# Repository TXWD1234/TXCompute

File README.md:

# **TXCompute**
***// Copyright (c) 2026 TXCompute. Licensed under the MIT License.***

TXCompute is a device to perform mathematical calculations. It is targeting to be a more powerful calculator, that don't only rely on buttons, but can handle complicated logic.
*This project is for the hackathon event [Fallout](https://fallout.hackclub.com) hosted by [Hackclub](https://www.hackclub.com).*

# Project Usage

## What it does
TXCompute device has a screen and USB ports that allow user to connect a USB keyboard to it, and input to a terminal-like text editor displayed by the screen. 

The input of user will be processed by a command line parser, which can handle simple commands, as well as TXCSL code.
If user input is TXCSL code, it will be forward to the TXCSL engine, which executes the input code, and outputs the execution result.

## How to use it
**To provide power:**
- Plug in an USB-C cable connecting with power into the USB-C socket

**To connect with keyboard:**
- Plug in an USB-A cable connecting with the keyboard (for wired keyboard) / wireless receiver (for wireless keyboard) into the USB-A socket

**To boot the device:**
- Press the power button on the device until the device is booted.

**To shutdown the device:**
- Enter `exit` or `shutdown` in the terminal
  ```
  exit
  shutdown
  ```
- or Press the power button until the device is shutdowned

**To perform a TXCSL calculation:**
- Enter the expression in the terminal directly
  ```
  1 + 2 * (5 + 2)
  ```
- or With prefix `csl`
  ```
  csl 1 + 2 * (5 + 2)
  ```

## How to build it
### Preparation
#### Hardware Parts
- An ESP32-S3-DevKitC-1 Devboard
- A LCD Screen that is 480x320px sized, and supports Parallel 8080 (i80) and ILI9488
- An USB-C receptacle
- An USB-A receptacle
- A push button
- A MOSFET Transistor
- 4 NPN Transistor
- 2 capacitors: 0.1uf, 10uf
- Several resistors: 10k, 5.1k
- Several wires

*See detailed information in [BOM](https://github.com/TXWD1234/TXCompute/blob/main/BOM.csv)*

#### Hardware Environment
- 3D Printer
  - Several filament
- Soldering Iron
  - Several solder

#### Software Environment
- ESP-IDF
- CMake
- Git
- TXLib
- (Optional) VSCode (With ESP_IDF plugin)
- (Optional) KiCad
- (Optional) Fusion
- (Optional) OrcaSlicer

### Procedure
#### Part 1: Shell
*Working Directory: `/Hardware/CAD`*
1. Use OrcaSlicer to process a component (an individual body) in the `Main.step` file
2. Send the result to your 3D printer
3. Wait for print to finish, and repeat for every component

#### Part 2: Software
*Working Directory: `/Software`*
1. Open the directory with VSCode
2. Connect the ESP32 Devboard to your computer
3. Run command `ESP-IDF: Build, Flash and Start a Monitor on Your Device` in VSCode:
   1. Ctrl+Shift+P open the palette
   2. Enter the command title `ESP-IDF: Build, Flash and Start a Monitor on Your Device`

#### Part 3: PCB
*Working Directory: `/Hardware/PCB`*
1. Contact a manufacturing company to fabricate the PowerButton PCB
   - Use the Gerber files in directory: `PowerButton/Gerbers`
   - Suggestion: Do this part in China

#### Part 4: Assembly
*Working Directory: `/Hardware`*
1. Place the ESP32 Devboard and the PowerButton PCB on their according foundation
   - Use screws to secure the mounting
2. Connect the components except the screen, according to the schematic: `PCB/Fallout.kicad_sch`
   1. Connect each pin of the USB-C receptacle to their respective GPIO pin
   2. Connect each pin of the USB-A receptacle to their respective GPIO pin
   3. Connect each pin of the PowerButton receptacle to their respective GPIO pin
3. Assemble the Hinge  

   1. Slide body Hinge_Left onto body Hinge_Edge_Left, such that the through hole of Hinge_Left is containing the extruding cylinder of Hinge_Edge_Left
   2. Slide body Hinge_Center_Left into the other side of Hinge_Left, such that the through hole of Hinge_Left is also containing the extruding cylinder of Hinge_Center_Left  

   3. Do the same thing with Hinge_Right, Hinge_Edge_Right and Hinge_Center_Right
   4. Slide each of the assembled hinge component onto body Screen/Body. Make sure the sunmao structure on the Hinge_Edge_* fit
   5. Insert the tenon part of the sunmao structure (body group: Hinge_Body_Connection) into the mortise in center created by the 4 overlaping rectangle holes
4. Connect the 2 main bodies
   1. Secure the hinge on the MCU/Body with screws in the indicated screw holes
   2. Run wires from the ESP32 through the hinge to the screen
5. Place the LCD Screen on it's foundation in the Screen/Body
   1. Place the LCD Screen
   2. Place the Cover (Body Cover) on top of the LCD Screen
6. Place the back plate (body MCU/Bottom)
   - Screw in the screws in the indicated location

# Project Story (Why it exists)
> *"Lower, lower, lower..."*

## My Programming Obsession
From the first day I started programming, I found myself constantly pursuing a direction involuntarily.
And that direction is **low level**.
Where I first started was already pretty low: C++ is almost everyone think the lowest.
But I am not satisfied with that.
Exploring more lower level things such as Windows API and OpenGL, while making my own library and creating data structures, considering architecture, building complex systems and engines... I am on the way toward the lowest level.

## Where Did TXCompute Came From
When I first heard about this hardware hackathon: Fallout, and the fact that I need to make a hardware project, the first thing I thought about is **calculator**.
This is the first time I tried hardware development; before I used to think that hardware are all logic gates.
And I thought using logic gates to make something would be really cool, and a really interesting challange.
In this case, a calculator would be a perfect project to do that. Implement the most basic adder, subtractor, and multiplier are exactly the tasks I was imagining.
Therefore I set my goal, and started reseaarching.

## The Design Struggle
After a bit of research, I quickly found out that there are way too many obstacles to achieve my original idea, therefore made it impossible.
The major problem is that logic gates are... kind of way too low, making them very hard to connect with other existing infrastructure.
After that realization, I was stuck in a design idea struggle. A design struggle about what I should make.
Not using logic gates just made everything feels so simple. MCUs can just perform the calculation, the entire project idea of a calculator just suddenly seems to be too easy and not impressive enough.
**I was worried about the project being too simple.**
For almost a week, I did not know what to do.
I was numbing myself by exploring hardware programming environment and new knowledge, but knowledge without usage is useless. And everytime I think about the project the only thing I felt is dilemma...
Until I finally found an solution. I do not need to make exactly the project I was planning to make before.
**If making the basic is too easy, then just expand on the basic.**
> **"Make it advanced, make it better."**

This is my conclusion. If just make a basic calculator is too easy with MCU, then make a better calculator, that has more feature, more capability, and faster.
When I realized that, I immediately had an idea:
Make a computation DSL, and an emulator for it.
Write a compiler and a virtual machine in the tight memory and performance constrained environment of embedded system is definitely hard enough... I thought.
So then, I start working.

## Back to Low Level
After 2 month of hardworking, TXCompute finally came close to the end.
During development, I found out that the project is actually not as simple as I thought.
The memory constraint really made software became a struggle. Architecture and structure design need to have awareness of the memory constraint, therefore much more complicated. I made several new data structure during development, and the entire project software design is also heavily optimized for tight memory.
At the very last, in the process of finishing up the project, I suddenly found out there is a unplanned component in the project: The PowerButton.
Brief explaination about the component: It is a hardware push button controling the power input of the device, but at the same time need to be able to be turned off by the software.
And as I developed deeper into this component, I learned the mechanics of transistors, and built logic gates (the NOT gate specificly) with it. Finally I utilized all these knowledge and created a PCB.
That's when I realized. I am back at what I was imagining at the start of the project: interact and make things with logic gates.
Additionally, even lower! I made the logic gate itself!
And that is exactly the pursuit of this project, as well as my programming career:
> *Lower, lower, and lower....*

# Credit
Auther: [TX_Jerry](https://www.github.com/TXWD1234)  
Assistant: [Justin Li](https://www.github.com/justinnova0915)  
Art Inspiration: The Matrix  
Event: [Fallout](https://fallout.hackclub.com), hosted by [Hackclub](https://www.hackclub.com)  
// Project by TXStudio  

# Project Documentation

This project consist of 4 main parts:
- The Hardware Assembly
- Fireware Infrastructure
- Terminal Engine
- TXCSL Languge Processor

And finally the `MainClass` that combines everything together.

*The purpose of this documentation is to provide an overview of the implementation, and an entry point of understanding the logic.*
*To understand the detailed logic, please read the source code, and take reference to the comments.*

## The Hardware Assembly

The TXCompute device, or the *"TXComputer"* consists of 2 parts:
- The 3D Printed Shell
- Circuit
- Hardware Parts

### Shell
*The 3D shell design took inspiration from my personal laptop: `Legion Y7000 IRX10`.*
The 3D printed shell is the hardware container containing all the wire connection from the circuit, who acts like the interface of the project for users.
The model design is highly focused on mechanical functionalities. Its implementation consists of:
- Hinge
- Circuit Foundation - support the wiring and the PCB to sustain it's position
- Several Connections
  - connect the screen to teh shell
  - connect the screen part to the hinge
  - connect the MCU part to the hinge
  - connect the front and back plate to the MCU part

*Highlight worth mentioning: The usage of sunmao in the connection.*

#### Hinge Design
The hinge is designed such that wires connecting the ESP32 and the screen (the display bus) can run through.
It has 2 hollow cylinders, one containing the other. The smaller one will be containing the wires.
The hinge allow a maximum rotation of 126 degree, and is physically stop by the MCU body when reached the limit. (Have to create a physical stop to prevent the hinge from laying flat because the material of 3D printing filament is neither strong enought nor accurate enough to make an actual self lock hinge.)

### Circuit
There are 2 main parts for the circuit: parts connection and the power button.

#### Parts Connection
Connect the components including:
- LCD Screen
- PowerButton
- USB-A / USB-C receptacle
to the ESP32 devboard.

#### PowerButton
The logic circuit that controls the power and life time of the device.
The circuit allow a push button to turn on and off the device, while when turned on, device can turn itself off as well.

## Firmware
*Also known as TXESP_Infrastructure.*

There are 4 branches in the firmware infrastructure, each serve a usage in the main class:
- TextRenderer
- USBKeyboardInputHandler
- Buffer
- PowerManager

### TextRenderer
TextRenderer is the highest level interface of the rendering pipeline, that is based off of the ILI9488 driver and ESP_LCD.
The dependency tree:
```
TextRenderer
FrameComposer
ILI9488DriverPanel
ESP_LCD
```

#### `ILI9488DriverPanel`
*This Driver is made according to the data sheet: https://www.hpinfotech.ro/ILI9488.pdf*
*It's basically just a wrapper of the io system.*
ILI9488DriverPanel manage the lowest level communication between the higher level firmware and the LCD screen hardware.
It has stores the commands to the hardware, and specificly focuses on these two jobs:
- Initialization of the LCD screen;
- Write data to specific location of the LCD screen's framebuffer.

Call `ILI9488DriverPanel::init()` to initialize; Call `ILI9488DriverPanel::draw()` to write pixels.

#### `FrameComposer`
Manage the bus and io, and also wraps around the `ILI9488DriverPanel`, bringing the render process one level higher.
It takes care of the transformation of the pixel data, manage the lifetime of the bus and io provided by ESP_LCD.
`FrameComposer` is the end of talking to hardware APIs. It fully wraps the configuration and initialization, leaving only an API `draw(Coord topLeft, Coord dimension, u16* data)` for the software to perform the rendering.

#### `TextRenderer`
Manage the pixel data, consists of a simple double buffer design, and the job of unpacking the bit-packed character data.
`TextRenderer` abstract the rendering pipeline one step furthur, now the software don't need to thing about the actual pixel data anymore, instead only the character that is being drawed need to be considered.
*This class is technically a software as it does not use hardware APIs directly, but I still considered it as firmware because it is such a low level component.*

#### Font
Because of the limited storage of ESP32, the font data is stored in bitmap, bit packed as one bit is one pixel.
The font data is in the form of a C array in hex with type `u8`, in a header file, along with a `size_t` constant containing the size of the font data, all in `constexpr const`.
The header file will be included by the user of the font.

The font file used in this project is generated by a 2 stage pipeline:
- convert ttf file into png file via a python script
- read the png image file and pack the color into bits via a C++ program

### USBKeyboardInputHandler
USBKeyboardInputHandler is the highest level interface of the keyboard input pipeline. It is based on HID and ESP's USB framework.
The dependency tree:
```
USBKeyboardInputHandler
USBFramework
ESP_USB; ESP_HID
```

#### `USBFramework`
Simplifies the pipeline of USB Host.
`USBFramework` provide a set of simplified init / uninit APIs to manage the driver and interface APIs.
It is simply just a wrapper around ESP_USB's API.

#### `USBKeyboardInputHandler`
*This class is made according to the data sheet: https://usb.org/sites/default/files/hut1_5.pdf*
*USBFramework is a generalized USB framework that work for any type of usb connection, while `USBKeyboardInputHandler` is made specificly for HID keyboard input.*
`USBKeyboardInputHandler` provide the interface and driver callback to the `USBFramework` to receive keyboard input.
After received the raw keyboard input report, `USBKeyboardInputHandler` also map the raw data into a custom key code set.
It also manages the pressing state of each key, tracking the state of each key pressed.
At the end, every time an report is updated, an user callback provided by the user of this class will be called with the parameter of the information of this key press event.
The overall design took inspiration and reference from GLFW 3. *Credit: `https://www.glfw.org`.*
`USBKeyboardInputHandler` is also a global state machine, adopted the design of *"pure static class"* from `USBFramework`.

#### Driver
Contains the implementation of `driverCallback_impl` and `interfaceCallback_impl`, as the lifetime manager of the process.
Also contain the essential enum types such as `Key`, `Action` and `Mod`, as well as `keyCodeTable`, which is the lookup table describing the translation between HID code and a uniformed code set that's corresponding to ASCII.

#### Logic
Handles:
- The decode process of the Modifiers
- The Action state
  - Release
  - Repeat
  - Press
- Current pressing key
  - Key cache
The core entry function is `handleReport_impl()`, which is being called by the `interfaceCallback` when an keyboard input event happens.

#### Interface
The user is only exposed to 3 functions:
- `init()`
	Initialize the entire system, including the `USBFramework`. *(it's actually just initing `USBFramework` but.. it's just for encapsulation)*
- `uninit()`
	Uninitialize the entire system, including the `USBFramework`.
- `setCallback(InputCallbackFunc_t func)`
	Set the event callback when a keyboard input event happens.

**`InputCallbackFunc_t`**:
```cpp
using USBKeyboardInputHandler::InputCallbackFunc_t = void (*)(
	USBKeyboardInputHandler::Key,
	USBKeyboardInputHandler::Action,
	USBKeyboardInputHandler::Mod); // key, action, mod
```

### Buffer
`buffer.hpp` is an wrapper around ESP_HEAP_CAPS, that provide a generalized API `allocate` and `free` with template to manage memory.
It also provide the memory managing wrapper for a few data structure from TXLib that are used in the project, including:
- `Buffer_GrowArray`
- `Buffer_CircularQueue`
- `Buffer_RingBuffer`

And a plain memory container `Buffer`.

### PowerManager
`PowerManager` is a small class that wraps the ESP_GPIO APIs, especially the intiialization setup, and gave the user a fast way to operate an pin's charge (voltage).
It is designed targeting to serve the power button functionality of the project.

## Terminal Engine

The Terminal Engine is a text render and input processor, that performs resemble a terminal.
It is designed targeting specificly for memory constrained environment, such as the embedded system environment in ESP32, following the KISS rule (Keep It Simple, Stupid).

---
Logics are separated into different classes, each with their own logic to consider: *"Do one thing and do it well"*.
Then the overall class `TemrinalEngine` combines all of the sub-logic classes into a set of uniform terminal APIs.

With that architecture in mind, there are 3 sub classes:
- `StringPool`
- `InputLine`
- `InputHandler`
And an overall class: `TerminalEngine`, which consist of 3 logical parts:
- Line Storage
- Input Pipeline
- Render Pipeline

### `StringPool`
The `StringPool` is a specialized implementation of an ring buffer.
There are 2 more features that it achieved beyond the classic ring buffer:
- Data entry grouping
- Automatic eviction

#### Data Layout
`m_data`: the buffer that stores the actual data
`m_meta`: the buffer that stores the meta data of each logical data group (object): where it start and how big is it.

#### Terminology:
> - Evict:
>   The operation of deleting old data to make space for incoming new data when buffer is full. The deleted data is always the oldest data, and one evition might delete multiple data entry depending on the condition
> - Object / Meta / Range:
>   These terms refers to an entry in `m_meta`, which is corresponding to a range of data in `m_data`. Conceptually simillar to a partition. In the case of the StringPool, it is a string.

#### Data Entry Grouping
Each object consist of one or more entry in `m_data`, and they are grouped together by logic. They are added to the buffer at the same time, and deleted together when eviction happens.
Because the size of each object is variadic, some object might be much bigger then others, or they might all have size of 1.

#### Automatic Eviction
The total memory usage of `StringPool` is fixed at construction. There are no runtime allocation after initialization.
Therefore, the size of `m_meta` and `m_data` are both fixed. Because the data entry grouping mechanism, especially because the variadic size, both `m_meta` and `m_data` have a potential of becomeing full.
Hence, there are 2 condition to invoke an eviction: `m_meta` is full or `m_data` is full.
In the case of MetaEviction (`m_meta` is full), the oldest and only the oldest object need to be deleted.
In the case of MemoryEviction (`m_data` is full), a range of objects need to be deleted, since the incoming object might have a size that is bigger then the oldest object.
Both evictions have a potential of leaving interspace (memory gap) between the oldest object and the second oldest object, since the incoming object's size might be smaller then size of the evicted object(s).

### `InputLine`
`InputLine` is a classic "gap buffer" inputer design, that provide APIs for the `TerminalEngine` to perform standard input actions (such as moving cursor, input characters, and deleting characters). It also provide a set of APIs for the `TerminalEngine` to query it's internal state and get the final inputed string when user finishes inputing.

#### Logic
There are 2 buffers in `InputLine`, each one has the capacity of the maximum length of one line in the terminal (which is set by `TerminalEngine`).
They are the left and right buffers. Intuitively, they stores characters to the left / right of the cursor.
Whenever a character is inputed, the char value is pushed to the back of the left buffer.
Whenever the cursor move left, the back element of left buffer (`left.back()`) is pushed to the back of right buffer. And vice versa for moving right.
The layout can be displayed like this:
```
Normal buffer:
[<<buf<<]
^       ^
front   back

InputLine's Gap Buffer:
[<<left<<]     |       [>>right>>]
^        ^     ^       ^         ^
front    back  cursor  back      front
```

### `InputHandler`
`inputHandler` is a wrapper of `tx::esp::USBKeyboardInputHandler` from TXESP_Infrastructure.
It convert the event callback style input into flattened buffer input, which can be easily parsed by `TerminalEngine`.

#### Reason
`tx::esp::USBKeyboardInputHandler` has a callback based input system, and that's not ideal for complex logic, because the callback is happened in a system level loop, which staling might cause problem.
Therefore, `InputHandler` is created. It provide `tx::esp::USBKeyboardInputHandler` a callback, which will push input event entries to a buffer provided by the `TerminalEngine`. It flattens the input stream, thereby the Terminal Engine can perform complex logic in async while not staling the system driver.

#### Logic
The buffer that holds the flattened input event data is the most complicated part of this sub-system.
Essentially, it is a ring buffer, that wraps around to the front when reached the back.
`TerminalEngine` and `InputHandler` share a same object of `tx::CircularQueue`. `InputHandler` push new element to the buffer when a new event happens; `TerminalEngine` read and delete the entries it read every update, creating a perfect producer-consumer cycle.
As long as `TemrinalEngine` don't stale while InputHandler is not `stale()`ed, the ring buffer will not collide.

### Line Storage
*Also know as LineBuffer.*

Stores the information of each line. Separated by `'\n'`.
It is a CircularQueue of type `Line_impl`.

#### Line_impl
A line could be either an entry in the `StringPool` or a string that's outside of the `TerminalEngine` (not owned by `TerminalEngine`).
There is only one u32 value in this struct. It could either be a `u32` id in the `StringPool`, or a `const char*` pointer since on 32 bit architecture a pointer is 4 bytes.
The last bit is used as the boolean flag to identify whether it's an id *(1)* or a pointer *(0)*.
*All of these just to save memory.*

#### `lineBufferEvict_impl()`
The line buffer is obviously fixed sized and will obviously fill up. If line buffer is filled up, but non of `StringPool`'s buffer is filled up, the eviction of line buffer will trigger. *Which is also know as LineBufferEviction. (following the naming convension of `StringPool`)*
It will first pop the last element of the line buffer, then try to communicate to `StringPool`, and delete the stored string that is corresponding to this deleting line entry, **if** this line entry is a id type.
*So in conclusion, this entire line buffer structure is a 3 way eviction system.*

#### `handleDeleteEvent_impl()`
This function is the callback function of `StringPool`. It handles the job of syncing the state of `StringPool` with lineBuffer.
Whenever a string (aka an object in StringPool terminology) is deleted, the corresponding line must be deleted as well.
Therefore, `lineBufferEvict_impl()` is called. And since meanwhile a line could also be an external string that don't belong to `StringPool`, a string pool eviction might invoke the deletion of multiple lines, since deletion must happen in chronological order, also since the line from `StringPool` must be delete, every line before the first `StringPool` line must be deleted as well.

#### The double lock between Line Buffer Eviction and StringPool Eviction
Because LineBuffer and StringPool are both ring buffer design, they all have possibility to trigger an eviction.
And the eviction need to sync with each other to prevent currupted data.
Since `handleDeleteEvent_impl()` calls `lineBufferEvict_impl()`, and `lineBufferEvict_impl()` also indirectly calls `handleDeleteEvent_impl()` by deleteing object from `StringPool`, a cycle is created. If not interrupted, an infinite recursive loop will stale everything.
Therefore in `TerminalEngine` there is a `m_state`, who contains 2 boolean flags, which are used for the 2 eviction to declare their state.
If one eviction is happening, and it calles the other eviction, the other eviction will not trigger the eviction back again: the infinite recursion loop is prevented by an if check.

### Input Pipeline

#### `TerminalEngine::poll()`
This is a public API called by the user - in the program sense - the higher layer of the TerminalEngine, which is the TXCompute main class.
`poll()` is the main entry of the async processing pipeline. When this function is called, the caller should expect the possibility of the input callback be called, and old references to the user input string to be invalidated (as they are stored in the `StringPool` of the TerminalEngine, which might delete some string entries to make free space for new spaces).
If `poll()` is not called for a long period of time, an exception might happen in the InputHandler, because the input buffer of the Terminal Engine is filled up. To prevent this, a pair of `stale()` / `unstale()` API is provided in `InputHandler` to ignore the input from source. ***You only need to manually call them if stale is planed to happen during input session.***
`poll()` copies the current input entries, and pop them from the buffer.
After that, the lock is released, and the processing of input begins.
`handleInputEvent_impl()` is called for every input event. Each input event is one key pressing, repeative pressing down, or releasing.

#### `TerminalEngine::handleInputEvent_impl()`
Process one key input event. It could be either pressing, repeative pressing down, or releasing.
If releasing, the event will be ignored.
Otherwise, if the key is printable, it will go through modifier modifications beforehand (such as CapsLock and Shift), and then be pushed into `InputLine` as a `char`.
If the key is non-printable, aka a function key, it will be processed in a `swtich`, determinding what action it is doing.
In this stage, all operations are methods of `InputLine`, except `Enter`, which triggers `handleNewLine_impl()`.

#### `TerminalEngine::handleNewLine_impl`
First it extracts the input string from `InputLine` and store it in the StringPool.
Then line buffer will be updated, potentialy triggering eviction: `lineBufferEvict_impl()`.
Finally, the input callback will be called with the input string stored in StringPool.

#### Sessions
There are 2 sessions in the terminal engine:
**Input Session:**
Start when `startInputSession()` is called.
End when terminal user presses enter or `endInputSession()` is called.
During input session, all `print()` will be ignored (including `printStatic()`), and inputHandler will be `unstale()`ed.

Default session. Start when TerminalEngine object is initiated, or input session had ended.
End when input session had started or TerminalEngine object is destroied.
During output session, all terminal user input will be ignored, and `print()` will be allowed.

### Render Pipeline
The render pipeline of the TerminalEngine consists of 4 parts:
- lhCache (line height cache) book keeping
- render state and cursor logic
- render events
- drawing characters and lines

#### Terminology:
| Word | Explaination |
|-|-|
Logical Line / Line_impl | the entry in lineBuffer, that represents one line without wrapping
Screen Line / Render Line | the actual displaying line of text on the screen, consider wrapping

#### lhCache
Front is top (of the screen); Back is bottom (of the screen)
Stores the height (screen line count) of every logical line that are visible on the screen.
It's index is linearly parallel to lineBuffer, meaning that the second entry in lhCache is corresponding to:
```cpp
m_lineBuffer[m_lhCacheState.topLine + 1]
```
lhCache represent the current display state, which serve for the scrolling logic.

##### `m_lhCacheState`
```cpp
struct LhCacheState_impl {
	/**
	 * topLine is index of the first Line_impl that is visible on
	 * the screen. It is also the index of Line_impl that the front() of
	 * lhCache is according to.
	 * topLineBegin is the index of the screen line that is the
	 * actual first line on the screen. it is the index within the range
	 * of the topLine object
	 */
	u32 topLine, topLineBegin, bottomLineEnd;
	/**
	 * the total amount of screen lines of all the logical lines that are
	 * currently visible on screen, including the invisible screen lines of
	 * the top and bottom logical line
	 */
	u32 screenLineCount;
} m_lhCacheState;
```

It is necessary to update screenLineCount whenever a push or pop to the lhCache happened.

#### RenderState
```cpp
struct RenderState_impl {
	/**
	 * cursorPos always points to the end of left buffer (exclusively), and
	 * points to the begin of right buffer (inclusively).
	 * Speaking in plain english: cursorPos is the first character of right
	 * buffer, which is also the character behind the last character of
	 * left buffer
	 */
	Coord cursorPos;
} m_renderState;
```
*Yeah an entire struct just to store one Coord. It's all for good practice trust.*

Cursor will wrap to the begining if moved horizontally to the end.

#### Render events
Event functions that have their name directly matching with the keyboard action event. *encapsulating inside encapsulation.*
The `handleInputEvent_impl` will call these event functions, which will perform their logic and update the graphics.

#### Drawing
Consist of simple grid -> pixel converter, line drawer and full redraw function

## TXCSL

TXCSL (TX Computational Scripting Language) is a bash-like, virtual machine based scripting language, which is capable of computing basic expressions.

*TXCSL is targeting to be a DSL for computation. It is an enhancement of regular calculators, but not a turing complete programming language.*

TXCSL operates in the pipeline described below:
> **Every line of code will be *compiled* into instructions, then executed.**
Even the result appears instantly, it had been through the process of compilation.

### Interface Data Structs

#### `Expression`
```cpp
struct Expression {
	std::span<Command> commandBuffer; // the commands / instructions
	std::span<num> constantBuffer; // constant values that are involved in the expression
	std::span<num> variableBuffer; // variable values that are involved in the expression
	tx::u32 registerCount; // the required registers when evaluating
	tx::u32 commandCount; // the count of commands / instructions
};
```
`Expression` is the **compiled binary instruction code** after compilation.
It will provide everything the `Evaluator` requires to calculate an output.
An object of this struct should be created before compilation, and all the buffers should be allocated with their respective size:
| Buffer Name      | Element Count |
| ---------------- | ------------- |
| `commandBuffer`  | 256           |
| `constantBuffer` | 64            |
| `variableBuffer` | 64            |

During compilation, the `commandBuffer` and `constantBuffer` will be populated.
But the `variableBuffer` will not be touched. The user need to provide values of the variables themself.

#### `CompileResult`
```cpp
struct CompileResult {
	tx::u32 commandCount;
	tx::u32 constantCount;
	tx::u32 variableCount;
	std::vector<std::string_view> varibaleNames; // for the caller of compile() to fill in the variabe buffer
};
```

#### How to populate `variableBuffer`

#### Note for then span design
You can have a big buffer that's bigger then the buffer's required size for each buffer.
Then you can store multiple compiled expressions. (The function design)
And that's what the `*Count`s in `CompileResult` is for.

### Compilation

*There is the where the major processing logic of TXCSL is.*
Every line of code in TXCSL is treated as expression, and will be processed by the `tx::csl::Compiler`.

#### The design pattern of the compilation
Each stage will have it's own class.
That class will be a temporary object, which will outputs a certain result of the stage.
The purpose of the class is to maintain it's own internal state (because they are all state machine design), and the temporary memory they allocate.

#### Compilation pipeline
The compilation pipeline flow is:
1. Raw string
2. BracketParser - compose bracket structure
3. Tokenlizer    - tokenlize raw string. identify and convert value
4. Compiler      - transform tokens into instructions, flatten the operation tree
The process of nested expressions will be lazy, meaning that it will not be processed until necessary. 
When the Compiler encounters an unexpanded expression, it will call the Tokenlizer again, and tokenlize the unexpanded expression.

*See detailed logic explaination in inlined comments of source files.*

#### APIs

`static CompileResult compile(std::string_view source, Expression& result)`

Compile the raw source string `source` into instruction code in `result`.
**Note:** the buffers in `result` should be allocated before calling this function. the buffers listed below will then be populated in the function.

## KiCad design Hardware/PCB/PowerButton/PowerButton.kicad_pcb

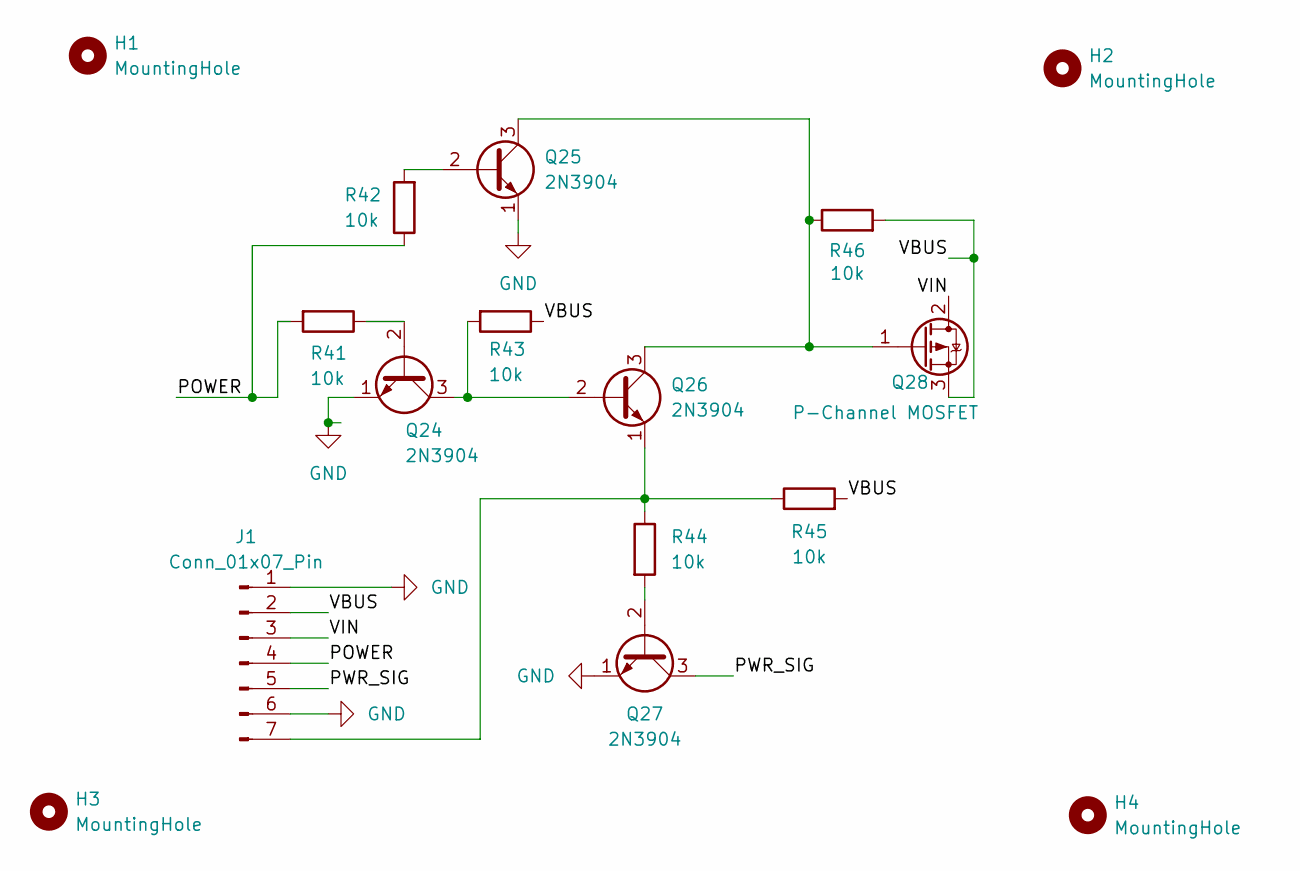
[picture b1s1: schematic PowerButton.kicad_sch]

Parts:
H1, H2, H3, H4: MountingHole; MountingHole_2.2mm_M2
J1: Conn_01x07_Pin; PinHeader_1x07_P2.54mm_Vertical
Q24, Q25, Q26, Q27: 2N3904; TO-92_Inline
Q28: P-Channel MOSFET; TO-220-3_Vertical
R41, R42, R43, R44, R45, R46: 10k; R_Axial_DIN0207_L6.3mm_D2.5mm_P7.62mm_Horizontal

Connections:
/POWER: J1.4, R41.2, R42.1
/PWR_SIG: J1.5, Q27.3 (C)
/VBUS: J1.2, Q28.3 (S), R43.1, R45.2, R46.2
/VIN: J1.3, Q28.2 (D)
GND: J1.1, J1.6, Q24.1 (E), Q25.1 (E), Q27.1 (E)
unnamed: J1.7, Q26.1 (E), R44.1, R45.1
unnamed: Q24.2 (B), R41.1
unnamed: Q24.3 (C), Q26.2 (B), R43.2
unnamed: Q25.2 (B), R42.2
unnamed: Q25.3 (C), Q26.3 (C), Q28.1 (G), R46.1
unnamed: Q27.2 (B), R44.2

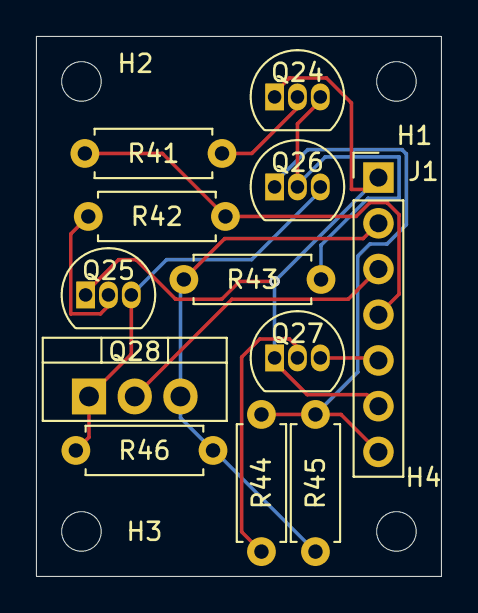
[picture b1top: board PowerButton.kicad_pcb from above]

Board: 2 copper layers, 22.5 x 30.0 mm, 16 parts (0 on the bottom side), 11 nets.

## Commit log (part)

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2026-05-26 TerminalEngine: Create class Buffer
2026-05-28 TerminalEngine: Debug and Fix StringPool
2026-05-30 TXESP: add buffer.hpp: Buffer<T> and Buffer_GrowArray<T> / Buffer_CircularQueue<T>
2026-05-30 TerminalEngine: refactor buffer structure to adapt the new buffer layout
2026-06-07 TextRenderer: add color rendering
2026-06-07 TerminalEngine: add clear()
2026-06-08 TerminalEngine: add documentation
2026-06-09 MainClass: add main class component - solve MainClass dependencies - create basic control pipeline
2026-06-09 ESP: add power manager for power button
2026-06-09 Fixing TXCSL Mis-include probelm
2026-06-10 add TextRenderer docuementation
2026-06-13 Create new Power Button Circuit to support hard shutdown
2026-06-14 Schematic Final
2026-06-15 Create PowerButton PCB
2026-06-15 Fix 3D model exporting problem
2026-06-17 Push before system switch - my arch crashed, have tgo switch to windows now
2026-06-17 Test adding pictures to Readme
2026-06-17 Add pictures to Readme
2026-06-18 Refactor PCB: Minimize Footprint
2026-06-18 Fixing Git issue: temporaryly delete Hardware/PCB
2026-06-18 Fixing Git issue: re-add Hardware/PCB
2026-06-20 Project Completion
2026-06-20 big fix after sanity check [1]
2026-06-20 bug fix after sanity check [2]
    Updated hinge assembly instructions and replaced PCB image.
2026-06-20 big fix after sanity check [3]
2026-06-20 bug fix after sanity check [4]
    Update assembly instruction order markdown format
2026-06-20 bug fix after sanity check [5] export step file and stl files
